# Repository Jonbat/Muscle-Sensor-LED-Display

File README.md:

## Muscle Sensor LED Display
This micro-controller project measures muscle contractions and displays it on a 32x32 LED screen. The harder you contract your muscle, the larger the wave! Any large enough muscle is compatible, such as the biceps, forearms, or even forehead muscles!
Check out my [youtube video](https://youtu.be/R8VW5WCSrXk) for some step-by-step installation instructions. 👌

## Motivation
Using adafruit's libraries, the slowest processor that can adequately run the [SPX-14633 32x32 matrix](https://sparkfun.com/products/14633) is 16MHz. By avoiding the libraries and driving each pin directly, as this code demonstrates, the LED matrix can adequately be driven on the 1 MHz processor of the atmega164p. 

## Design
The schematic and board files were designed for the Atmega164p and the SPX-14633 32x32 LED screen. Another microcontroller can be used, and this schematic should make a good reference. Because of the fast clock and refresh rate needed to drive the 32x32 LED screen, I would  recommend using a micro controller with a 1 MHz processor and higher. An optional RS-232 serial interface is included for debugging and JTAG interface for on-board programming of the Atmega 164P.

#### Physcial Board

#### Schematic

#### Board Design

## Materials
Muscle Sensor:
* [MyoWare Muscle Sensor  ($37.95)](https://www.adafruit.com/product/2699)
* [Surface EMG Electrodes ($4.95)](https://adafruit.com/product/2773)
* 1x3 Pinhead

Micro-controller:
* [Atmega164p ($3.79)](https://microchip.com/wwwproducts/en/ATmega164P)

LED Panel:
* [32x32 LED Panel- 1:8 scan rate ($14.95)](https://sparkfun.com/products/14633)
* 2x8 pinhead

UART Debugging (optional):
* RS-232 serial interface
* Max232            

On-board Programming (optional):
* Any JTAG programmer to program micro controller
* 2x5 pinhead

Power:
* 7805 voltage regulator
* 9-Volt battery
* Barrel connector

Other (see schematic):
* 2 Buttons
* Several 0.1 μF capacitors
* Several resistors

## Code
The included micro-controller C code does not use any libraries, besides avr/io.

## Installation Help
* [Myoware muscle sensor set-up](https://learn.adafruit.com/getting-started-with-myoware-muscle-sensor)
* [Matrix hook-up guide](https://learn.sparkfun.com/tutorials/rgb-panel-hookup-guide)

## How it works
* [1:8 Scan rate panels](https://www.sparkfun.com/sparkx/blog/2650)

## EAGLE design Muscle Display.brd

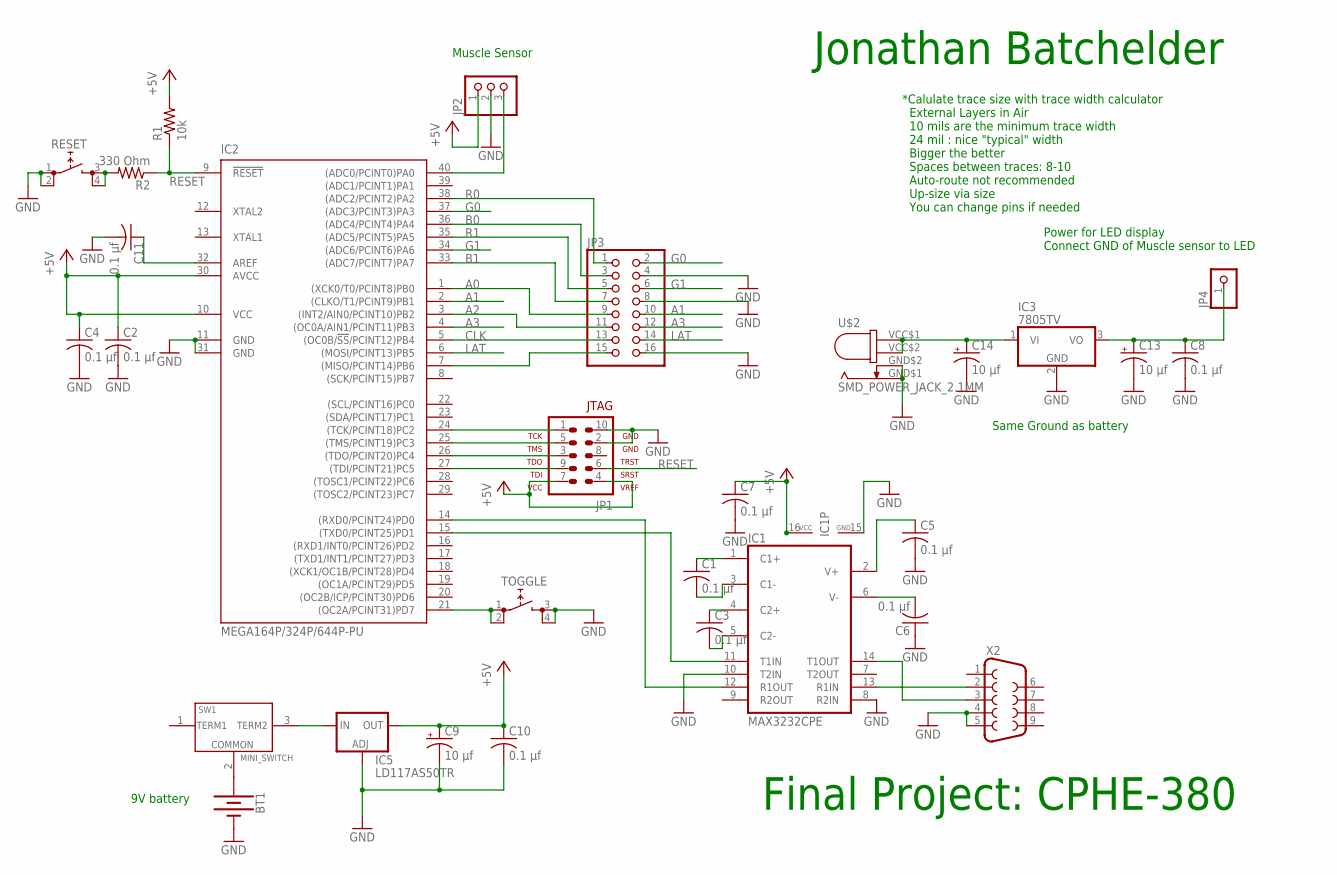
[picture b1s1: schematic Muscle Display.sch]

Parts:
BT1: BATTERY-9V; BATTCON_9V
C1, C2, C3, C4, C5, C6, C7, C8, C11: 0.1 μf; C050-025X075
C9: 10 μf; PANASONIC_C
C10: 0.1 μf; C0805
C13, C14: 10 μf; E2,5-5
IC1: MAX3232CPE; DIL16
IC2: MEGA164P/324P/644P-PU; DIL40
IC3: 7805TV; TO220V
IC5: LD117AS50TR; SOT223
JP1: AVR-JTAG-10
JP2: PINHD-1X3; 1X03
JP3: PINHD-2X8; 2X08
JP4: PINHD-1X1; 1X01
R1: 10k; 0207/10
R2: 330 Ohm; 0207/10
RESET: PUSHBUTTON; TL1105SP
SW1: MINI_SWITCH
TOGGLE: PUSHBUTTON; TL1105SP
U$2: SMD_POWER_JACK_2.1MM; SMD_POWER-JACK_2.1MM
X2: F09H

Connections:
+5V: C2.1, C4.1, C7.1, C9.+, C10.1, IC1.16 (VCC), IC2.10 (VCC), IC2.30 (AVCC), IC5.4 (OUT), JP1.4, JP1.7, JP2.1, R1.2
A0: IC2.1 ((XCK0/T0/PCINT8)PB0), JP3.9
A1: IC2.2 ((CLKO/T1/PCINT9)PB1), JP3.10
A2: IC2.3 ((INT2/AIN0/PCINT10)PB2), JP3.11
A3: IC2.4 ((OC0A/AIN1/PCINT11)PB3), JP3.12
B0: IC2.36 ((ADC4/PCINT4)PA4), JP3.3
B1: IC2.33 ((ADC7/PCINT7)PA7), JP3.7
CLK: IC2.5 ((OC0B/!SS!/PCINT12)PB4), JP3.13
G0: IC2.37 ((ADC3/PCINT3)PA3), JP3.2
G1: IC2.34 ((ADC6/PCINT6)PA6), JP3.6
GND: BT1.-, C2.2, C4.2, C5.2, C6.1, C7.2, C8.2, C9.-, C10.2, C11.2, C13.-, C14.-, IC1.8 (R2IN), IC1.10 (T2IN), IC1.15 (GND), IC2.11 (GND), IC2.31 (GND), IC3.2 (GND), IC5.1 (ADJ), JP1.2, JP1.10, JP2.2, JP3.4, JP3.8, JP3.16, RESET.1 (0), RESET.2 (0), TOGGLE.3 (1), TOGGLE.4 (1), U$2.GND$1 (OUTSIDE$1), U$2.GND$2 (OUTSIDE$2), X2.4, X2.5
LAT: IC2.6 ((MOSI/PCINT13)PB5), JP3.14
unnamed: C1.1, IC1.1 (C1+)
unnamed: C3.2, IC1.5 (C2-)
unnamed: C3.1, IC1.4 (C2+)
unnamed: IC1.13 (R1IN), X2.2
unnamed: BT1.+, SW1.2 (COMMON)
unnamed: IC5.3 (IN), SW1.3 (IO3)
unnamed: R2.2, RESET.3 (1), RESET.4 (1)
unnamed: IC2.24 ((TCK/PCINT18)PC2), JP1.1
unnamed: IC2.25 ((TMS/PCINT19)PC3), JP1.5
unnamed: IC2.26 ((TDO/PCINT20)PC4), JP1.3
unnamed: IC2.27 ((TDI/PCINT21)PC5), JP1.9
unnamed: IC2.21 ((OC2A/PCINT31)PD7), TOGGLE.1 (0), TOGGLE.2 (0)
unnamed: IC1.14 (T1OUT), X2.3
unnamed: C1.2, IC1.3 (C1-)
unnamed: C8.1, C13.+, IC3.3 (VO), JP4.1
unnamed: C5.1, IC1.2 (V+)
unnamed: C6.2, IC1.6 (V-)
unnamed: C14.+, IC3.1 (VI), U$2.VCC$1 (INSIDE$1), U$2.VCC$2 (INSIDE$2)
unnamed: IC1.12 (R1OUT), IC2.14 ((RXD0/PCINT24)PD0)
unnamed: IC1.11 (T1IN), IC2.15 ((TXD0/PCINT25)PD1)
unnamed: C11.1, IC2.32 (AREF)
OE: IC2.7 ((MISO/PCINT14)PB6), JP3.15
R0: IC2.38 ((ADC2/PCINT2)PA2), JP3.1
R1: IC2.35 ((ADC5/PCINT5)PA5), JP3.5
RESET: IC2.9 (!RESET), JP1.6, R1.1, R2.1
SENSOR_INPUT: IC2.40 ((ADC0/PCINT0)PA0), JP2.3

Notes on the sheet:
Final Project: CPHE-380
Muscle Sensor
9V battery
Jonathan Batchelder
*Calulate trace size with trace width calculator External Layers in Air 10 mils are the minimum trace width 24 mil : nice "typical" width Bigger the better Spaces between traces: 8-10 Auto-route not recommended Up-size via size You can change pins if needed
Power for LED display Connect GND of Muscle sensor to LED
Same Ground as battery

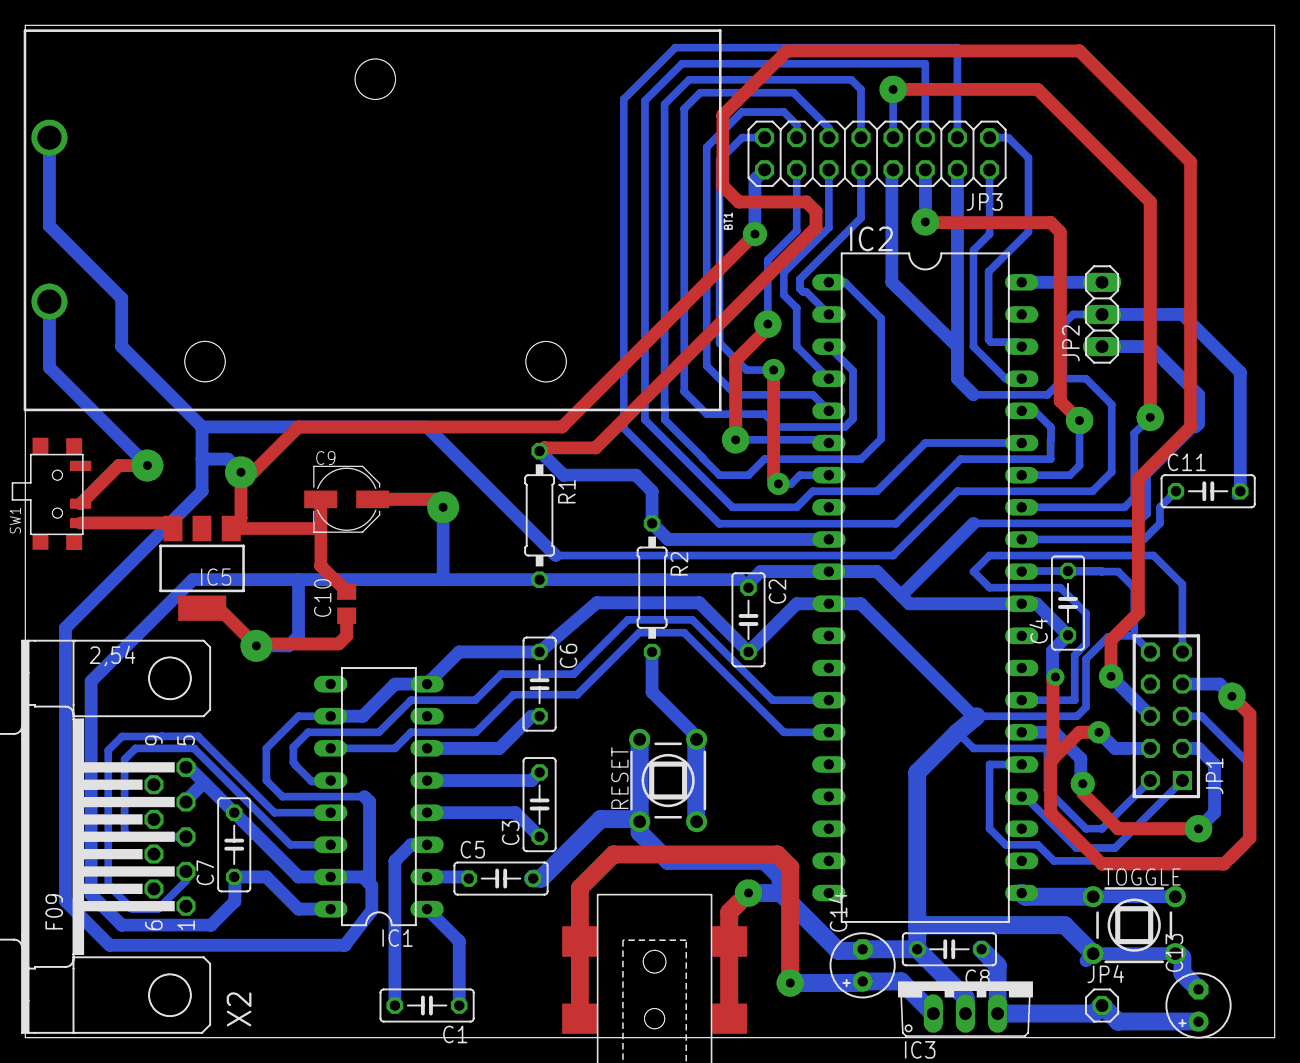
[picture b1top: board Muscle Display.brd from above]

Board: 2 copper layers, 98.7 x 80.0 mm, 29 parts (0 on the bottom side), 38 nets.

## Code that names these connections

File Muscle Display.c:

/*
 * Muscle Sensor.c
 *
 * Created: 12/6/2018 10:24:02 AM
 * Author : Jonathan Batchelder
 */ 

#include <avr/io.h>
#include <util/delay.h>

#define DATAPORT PORTA
#define CLK PB4
#define OE  PB6
#define LAT PB5
#define A  PB0
#define B  PB1
#define C  PB2

#define R1 PA2
#define R2 PA5
#define G1 PA3
#define G2 PA6 
#define B1 PA4
#define B2 PA7

void matrix_init () {
	DDRA = 0xFC;  		// all bits outputs, except PA0 (sensor) and PA1 (unused)
	DDRB = 0xFF;
	PORTA = (1 << PA0);	// pull-up resistor
}

void ADC_init () {
	ADCSRA = (1 << ADEN);    				// enable ADC
	ADCSRA |= (1 << ADATE) | (1 << ADSC);   // start conversation
	ADMUX = (1 << REFS0);
}

uint16_t ReadADC() {
	uint8_t LS_data = ADCL; 
	uint8_t MS_data = ADCH;
	uint16_t adc_data = (MS_data << 8) | LS_data;
	return adc_data;
}


int main(void) {
	uint8_t C1 = B1;		// blue on default
	uint8_t C2 = B2;
	uint8_t addramask = ~(1 << A);
	uint8_t addrbmask = ~(1 << B);
	uint8_t addrcmask = ~(1 << C);
	matrix_init();
	ADC_init();
	
	uint16_t wave_multiplier;
	uint8_t row = 8;				   		// keep track of which row
	
	while (1) {
		uint16_t wave_val = ReadADC() / 2;	// currently configured for 0 - 1696
		for (int row_line = 8; row_line > 0; row_line--) {

			for (int i = 63; i > -1; i--) { // Display needed to be flipped: for (int i = 0; i < 64; i++) 

				DATAPORT &= ~(1 << C1);
				DATAPORT &= ~(1 << C2);
				 
				//  1010 (Display Algorithm)
				if (i >= 16 && i <= 47) {    // 1000
					if ( wave_val > ( (i - 16) * row_line ) ) {
						DATAPORT |= (1 << C2);
					} 					     // 0010
					if ( wave_val > ( (i - 16) * (row_line + 18) ) ) {
						DATAPORT |= (1 << C1);
					}
				}
				// 0101
				else {
					if ( i > 47 ) {
						wave_multiplier = i - 32;
					} else {
						wave_multiplier = i;
					}						// 0100
					if ( wave_val > (wave_multiplier * (row_line + 8)) ) {
						DATAPORT |= (1 << C2);
					}						// 0001
					if ( wave_val > ( wave_multiplier * (row_line + 24)) ) {
						DATAPORT |= (1 << C1);
					}
				}
				PORTB &= ~(1 << CLK); // tick, clock lo
				PORTB |= (1 << CLK);  // tock, clock hi
			}
			// Update row
			if (++row >= 8) {		  // reset row to 0 every 8 times
				row = 0;
			}
			
			PORTB |= (1 << OE);		 // disable output when loading
			PORTB |= (1 << LAT);     // latch data loaded
			
			// next row
			if(row & 0x1)   PORTB |= (1 << A);
			else          	PORTB &= addramask;   
			if(row & 0x2)   PORTB |= (1 << B);
			else            PORTB &= addrbmask;
			if(row & 0x4)   PORTB |= (1 << C);
			else            PORTB &= addrcmask;
			
			PORTB &= ~(1 << OE);	// output enabled
			PORTB &= ~(1 << LAT);	// latch down, ready for more
		}
	}
}

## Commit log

2020-12-17 Detatiled images for readme

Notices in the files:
parts and their libraries:
SparkFun-Batteries: Licensing: Creative Commons ShareAlike 4.0 International - https://creativecommons.org/licenses/by-sa/4.0
